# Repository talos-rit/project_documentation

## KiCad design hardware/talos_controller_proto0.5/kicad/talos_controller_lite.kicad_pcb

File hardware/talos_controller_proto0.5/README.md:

# Talos controller, prototype 0.5

A controller board for the Scorbot ER-V and ER-4pc educational arms (the Talos-RIT project's two robots), built to cost
less than the first Talos controller ([`../talos_controller/`](../talos_controller/README.md)). It drives all seven
motors of the robot (the five arm motors, the gripper and the slide rail) from an ESP32-S3-DevKitC-1 plugged into
sockets, on a 141 × 139.6 mm two-layer board that JLCPCB assembles: seven DRV8874 motor driver chips soldered on, the
encoders counted by the DevKit itself, shift registers and an analogue multiplexer in place of the expander, counter
and ADC chips, power from one 24-pin PC supply plug, and a MOTORS ON relay latch behind an external emergency stop.

The board speaks to the rest of the system through the DevKit's own USB sockets, like the first Talos controller: the
Raspberry Pi "operator" software in Eshed mode (the Eshed controller's own serial dialect), or the ROS 2 stack in
External mode (a protobuf link).

> [!warning] Status, 23 November 2026
> **Designed, checked and reviewed; never built and never powered.** The board passes KiCad's design-rule check with
> no error and nothing unconnected (six explained warnings, section 8), and separate scripted checks of the e-stop
> wiring and of the encoder lines. A separate review pass of the layout found three major and five minor points in
> the copper; all were fixed, and a re-check of the fixed board found nothing that should hold an order. JLCPCB's order page
> has seen these exact files: its parts page matched all 29 parts lines, and its placement preview showed every
> polarised part the right way round. Neither cart on [`purchase_options.md`](purchase_options.md) has been paid.
> **The firmware for this board is not published yet** (section 4). It has run on a chip only as a bench test on a
> bare DevKit: the test of the three software-counted encoders, which passed twice. Everything else (the shift
> registers, the multiplexed current reading, the drivers, the heat, the real encoders' signals) is first seen on the
> first board. Read everything here as "designed and checked, not yet proven"; section 5 exists because the first
> board is the first test of the design.

North is up. Along the west edge: the 24-pin PC supply plug `J2`, the two motor-rail capacitors `C1` and `C2`, the
MOTORS ON button `SW3`, the external e-stop terminal `J4`, the `PS_ON` jumper `JP1` and the ground post `J6`. Along the
north edge: the motor fuse `F1` ("5A MAX"), the relay `K1`, the three e-stop chain test pads (CHAIN, GND, LOOP) and the
rail terminal `J8`. In the middle, the seven drivers in a column, motor 7 at the top (`U14`) to motor 1 at the bottom
(`U8`), each with its fault lamp, its two direction lamps and its name printed beside it. East of them the shift
registers `U2`, `U3`, `U5`; then the DevKit `U1` with its USB end at the north edge, the select register `U6` under it
and the multiplexer `U7` east of it. Below the DevKit the row of ten status-LED positions, then the encoder and switch
blocks, and the 50-pin robot connector `J1` on the south edge.

## How it differs from the first Talos controller

| | First Talos controller, rev 0.5 | **This board, prototype 0.5** |
| --- | --- | --- |
| Board | 265 × 210 mm, two layers, all through-hole | **141 × 139.6 mm, two layers**, surface-mount parts placed by JLCPCB, the through-hole parts (163 joints) fitted by hand |
| Motor drivers | plug-in modules (the Talos driver module or a Pololu G2 18v17) | **one DRV8874 chip per motor, soldered on by the factory**; each limits its own current at 2.93 A (2.75 to 3.2 A over part tolerances) |
| Motor current | set by the module | **about 1.5 A in all seven motors at once without end, about 2 A in one or two** (a heat estimate, section 8) |
| Encoders | one LS7366R counter chip per motor | **the DevKit counts them itself**: four on its pulse counters (motors 1 to 4), three in software (motors 5, 6, 7) |
| Inputs, outputs, ADC | two MCP23017 expanders, two ADS1015 ADC boards | **two 74HC595 and two 74HC165 shift registers** on one SPI bus; the seven motor currents and the rail voltage through **one 74HC4051 multiplexer** into one ADC pin of the DevKit |
| Supply | 24-pin plug for 5 V, the 4-pin CPU lead for the motors, `F1` 7.5 A | **one 24-pin PC supply plug for everything**; the motors' 12 V on its pins 10 and 11; **`F1` 5 A, never more**; the firmware holds the sum of the motor currents to **4 A** |
| Emergency stop | IDEC mushroom on the board, an external loop, two relays | **external e-stop only** (screw terminal `J4`, required), **one two-pole relay**, and the drivers held asleep whenever the relay's coil is off |
| Status lights | ten through-hole pixels | per motor a red fault lamp and a pair of green direction lamps, a 5 V lamp and a motor-power lamp, all placed by JLCPCB; **ten optional 2 × 2 mm status LEDs**, fitted by hand with hot air |
| Encoder supply sense | a comparator on two DevKit pins | a divider on a shift-register input ("5 V present") |
| Firmware | the controller firmware's default board | its own board variant, not yet published (section 4) |

The robot connector `J1` is the same 50-pin socket with the same pin-out for the ER-V and the ER-4pc, and the rail
terminal `J8` is the same 8-way terminal in the same pin order.

## What is in this folder

| File | What it is |
| --- | --- |
| `README.md` | this guide |
| `parts.md` | the parts list: what JLCPCB places, what you fit by hand, the makes that fit |
| `purchase_options.md` | the two carts of 23 November 2026 (JLCPCB and Digi-Key) with every line |
| `fab/talos_controller_lite_proto0.5_gerbers.zip` and `.sha256` | the manufacturing files (Gerbers and drill files): the zip to order from. Its name is the one on the order |
| `fab/jlcpcb_bom.csv`, `fab/jlcpcb_cpl.csv` | the parts list and placement file for JLCPCB's assembly (29 lines, 241 placements) |
| `fab/hand_assembled.csv` | the parts JLCPCB does not place: what you fit yourself, with the solder joints of each |
| `fab/digikey_cart_two_boards.csv` | the Digi-Key list for two boards with spares, ready for "Upload a list" |
| `schematic.pdf` | the schematic: every part with its pins, each pin labelled with its net name |
| `images/` | `print_top.png` and `print_bottom.png` (the printed side as it will look; the bottom as seen from below), `copper_top.png` and `copper_bottom.png` (the two copper layers) |
| `kicad/` | the KiCad project: board, schematic, project file, the footprints drawn for this board and their library table. KiCad 7 format; later versions open and upgrade it |

The KiCad files keep the project's working name, `talos_controller_lite`. The schematic is generated: each part is
drawn as a pin table with net labels, not as a drawn circuit.

## What you need

- **The two orders** on [`purchase_options.md`](purchase_options.md): JLCPCB (boards, the surface-mount parts and their
  assembly) and Digi-Key (the through-hole parts). Both are for two complete boards with spares.
- **Hand soldering:** twelve through-hole positions a board (the DevKit's two socket strips counted as one), 163 joints. No surface-mount soldering is needed unless you fit
  the optional status LEDs. A multimeter; a bench supply with a current limit helps for the checks of section 5.
- **An ATX PC power supply** with a 24-pin main lead. The 4-pin CPU lead is not used.
- **An external emergency-stop button** with a normally closed contact and its cable, for `J4`. The board has no stop
  button of its own (section 6).
- **For the rail:** an adapter from the rail cable's D9 plug to bare wires for `J8`, or the plug cut off (section 6).
- **Six M3 screws and standoffs** for the six mounting holes, with plain or nylon washers on the top side (no toothed
  lock washers).
- A computer with ESP-IDF v5.5.3 to build and flash the firmware, and two micro-USB **data** cables.
- A Raspberry Pi running the operator, or a PC with the ROS 2 stack.

**Not in the carts, and needed:**

- **One ESP32-S3-DevKitC-1 per board.** Any variant that is not a "...V" part fits: N8, N8R2, N8R8, N16R8 and their
  1U versions (an antenna socket in place of the printed antenna; the board does not use the radio). The R8 variants
  use GPIO35 to GPIO37 for their memory, and the board leaves those three pins unconnected. **A variant ending in V
  (N16R8V, N32R16V) must not be used**: it runs GPIO47 and GPIO48 at 1.8 V, and this board uses both (encoder 4 and
  the status-LED data).
- **Optional: ten status LEDs, 2.0 × 2.0 mm, WS2812-type** (positions `D21` to `D28`, `D49`, `D50`), fitted by hand
  with hot air; JLCPCB's Economic assembly does not place this kind of part, so the factory leaves the positions empty
  and the board works without them. The footprint and the firmware's timing were drawn for the Worldsemi
  WS2812C-2020-V6 (5 mA per colour); the Worldsemi **WS2812B-2020** fits the same pads with the same pin map and
  timing, at **12 mA per colour**. What they need:
  - **Pin 1 on the pad with the printed dot** beside it. Pins: 1 data out, 2 ground, 3 data in, 4 supply (5 V).
  - **They are moisture sensitive** (class 5a in Worldsemi's sheet): bake loose parts before hot air (Worldsemi
    gives 120 °C for 4 h) or take the risk on a cheap part.
  - **Fit one first** and check that it lights and passes data on before fitting the others.
  - **Keep the firmware's brightness cap** (32 of 255). At the cap ten WS2812B-2020 take about 50 mA; at full white
    they would take about 0.37 A, which the 5 V fuse `F3` carries but with little margin in a warm box.

## 1. Order the board

Upload `fab/talos_controller_lite_proto0.5_gerbers.zip` to JLCPCB as it is; check its sha256 against
`fab/talos_controller_lite_proto0.5_gerbers.zip.sha256` first if you copied it around. The cart of
[`purchase_options.md`](purchase_options.md) was made with these options:

| Option | Choose |
| --- | --- |
| Layers, size | 2 layers; 141 × 139.6 mm is read from the files. The bottom edge has a notch 69 × 2.8 mm under the robot connector, on purpose (section 3) |
| Thickness, colour | 1.6 mm, green |
| Copper | 1 oz outer copper (every current and heat figure here assumes 1 oz) |
| Surface finish | the cart was priced with JLCPCB's default, leaded HASL; lead-free HASL is a choice on the order page, not priced here |
| Design limits | tracks and gaps 0.2 mm or more, vias 0.6 / 0.3 mm, smallest hole 0.3 mm: inside JLCPCB's standard two-layer service |
| Order number | **"Specify a location"**: the board has a text `JLCJLCJLCJLC` under its name for it; otherwise JLCPCB prints the number where it likes |
| Quantity | 5 bare boards, 2 of them assembled (the cart's choice) |

Expect one remark: 34 part references on the top side are printed 0.8 mm high, under JLCPCB's recommended 1.0 mm.
All of them are references of parts the factory places; every function text is 1.0 mm or more.

**Assembly.** PCB assembly, **Economic, top side**. Upload `fab/jlcpcb_bom.csv` as the BOM and `fab/jlcpcb_cpl.csv`
as the placement file. The parts page should read "29 parts detected, 29 parts confirmed"; eight of the lines are
Extended parts (with JLCPCB's fee per part type): `D1`, the BAT54S, `F2`, `F3`, the 47 Ω 1 W resistor, the 74HC165,
the 74HC4051 and the DRV8874. JLCPCB adds its own spares or minimum quantities on some lines. A line it cannot match
or has no stock for must be resolved before ordering: every placed part is surface-mount, and the drivers need hot
air.

Choose **Confirm parts placement = Yes** and check the preview: the seven drivers (pin 1 at the south-east, the chips
are turned half round), the five SOIC-16 chips `U2`, `U3`, `U5`, `U6`, `U7` (pin 1 at the north-west), the fourteen
BAT54S, `Q3` and `Q4`, the 23 lamps (the preview's "+" at the anode, the end opposite pad 1) and the diodes `D1`, `D4`,
`D20` (the band at pad 1). The ten status-LED positions stay empty.

## 2. Order the parts

[`purchase_options.md`](purchase_options.md) has both carts line by line. For Digi-Key, upload
`fab/digikey_cart_two_boards.csv` with "Upload a list"; it is the list the cart was made from (14 lines, two boards,
with spare fuses, relay, switch and capacitors). [`parts.md`](parts.md) has every part, the makes that fit and the
rules that must not be broken when substituting. The three most important:

- **`F1` is a 5 A blade fuse, never more** (section 6 says why).
- **The supply header `J2`**: try the PC supply's plug in a loose header before soldering it (Würth's make).
- **The robot connector `J1`**: seat it in a bare board before soldering (HARTING's make).

## 3. Assemble

JLCPCB places every surface-mount part. You fit the through-hole parts of `fab/hand_assembled.csv`, all from the top,
soldered on the bottom, where every through-hole pin has its name printed. Lowest parts first:

1. **`JP1` and `J6`**: two 2-pin pieces cut from the 1×40 header strip. A shunt on `JP1` ("PS_ON, FIT = ON") turns
   the supply on with its own mains switch.
2. **The DevKit's two 1×22 socket strips** (`U1`). Solder two end pins of each, check that the DevKit seats with its
   USB end at the printed "DEVKIT USB END" and triangle, then the rest.
3. **`SW3`, MOTORS ON** (Omron B3F-4055; its two bosses go into the two holes), then its key top.
4. **`C1` and `C2`, 220 µF 35 V. Mind the polarity**: the long lead (+) goes in the square pad, marked "+" on both
   sides; the filled half of the printed outline is the ground side.
5. **`J4`, the e-stop terminal** (2 pins, 5.08 mm). If the Same Sky part does not go into the holes, two wires can be
   soldered in its place.
6. **`J8`, the rail terminal**, wire entry towards the north edge. Hold the part against the board before soldering.
   Its motor pins (`M+`, `M−`) carry the rail motor's 12 V: look at every joint for a bridge.
7. **`F1`, the fuse holder**, and **`K1`, the relay**.
8. **`J2`, the 24-pin supply header.** **First push the PC supply's plug into the loose header** and check it latches
   (Würth's data sheet gives the board's hole pattern but does not say the part mates with the supply's plug; Molex's
   39-30-1240 is a verified second make, see `parts.md`). Its pegs are plastic: a substitute with a metal board-lock
   must not be used, because 12 V and e-stop copper pass close to the peg holes. The housing is flush with the west
   edge.
9. **`J1`, the robot connector, last.** **Seat it in the bare board before soldering**: HARTING's 09 66 552 6616, on
   the Digi-Key list, has a threaded flange that reaches below the board's top face, which is why the bottom edge
   steps back 2.8 mm under the connector; its fit was checked against HARTING's 3D model, not a real part. Amphenol's
   DD50S565MTLF fits as well (with two screwlock kits). The pads are close together (0.23 mm to the nearest other
   copper at one place): solder with a fine tip and inspect every joint under a magnifier.
10. **The fuse**: a 5 A ATO blade into `F1`. The 0.5 A chain fuse `F2` and the 1.5 A resettable fuse `F3` are
    soldered by the factory.
11. **The DevKit**, with its USB end at the printed "DEVKIT USB END" and triangle (the north edge). **Turned round it
    still fits, and its 5 V and ground pins land on other nets.**
12. **Mounting:** six M3 screws with plain or nylon washers on the top side, no toothed lock washers. No copper on
    the outer layers comes within 3.6 mm of a hole's centre, so metal washers are fine.

Trim the e-stop wires clean when you clamp them in `J4`: its two pins are 2.5 mm apart, and a wire strand across them
bypasses the external stop without a sign.

## 4. Firmware

> [!warning] Not published yet
> This board needs its own variant of the Scorbot Controller firmware, the firmware of the first Talos controller
> ([talos-rit/esp-driver](https://github.com/talos-rit/esp-driver)): seven motors, the pin plan below, the
> shift-register words, three software-counted encoders and the multiplexed current reading. That variant is written
> but not published: **not yet implemented in the published firmware (prototype 0.5 board variant, to be
> published)**. It passes the firmware's host tests and compiles for the ESP32-S3 with ESP-IDF v5.5.3 with no warnings;
> on a chip it has run only as the encoder bench test below. Do not flash the first Talos controller's firmware onto this board: its pins are
> not this board's.

**The encoder bench test.** On a bare DevKit with nothing on its pins, the chip makes a quadrature signal on the three
software-counted encoders' pin pairs and a hardware pulse counter counts the same signal as the reference, while the
firmware is kept busier than in service. It passed twice, with the software count equal to the hardware count and no
illegal step at every rate from 8,000 to 128,000 counts a second (31.7 million edges on each encoder); 8,000 counts a
second is the assumed top speed of one encoder (80 counts per motor turn at an assumed 6,000 motor turns a minute,
not measured). The encoders are handled by an interrupt at level 5; the firmware must keep it (lower levels lost
counts on the bench). The test does not show three encoders moving independently (its three pairs carried one
signal), the real encoders' signals, or a line that chatters.

**The link.** The DevKit's socket marked **UART** is the link to the Pi and the flashing port; the socket marked
**USB** is the console. In Eshed mode the board speaks the Eshed controller's serial dialect at 9600 baud, so the
operator on the Pi runs unchanged; External mode is the protobuf link used by the ROS 2 stack. The ESP32-S3's ROM
prints a boot log on the UART socket at every reset; the first Talos controller's guide (section 4) has the eFuse
setting that silences it.

**eFuses never to burn on a DevKit used here:** `STRAP_JTAG_SEL` (GPIO3 is an encoder input on this board; with that
fuse, its level at reset would move JTAG onto GPIO39 to GPIO42, which are `PWM5`, encoder 2 and `SLP`) and
`DIS_USB_JTAG` (the console).

### Pin plan

The contract between the board and the firmware. No GPIO is left free.

| GPIO | Net | Use |
| --- | --- | --- |
| 1, 2 / 41, 40 / 4, 5 / 47, 21 | `ENC1A`/`B` to `ENC4A`/`B` | encoders 1 to 4, on the pulse counters |
| 11, 12 / 6, 7 / 8, 3 | `ENC5A`/`B`, `ENC6A`/`B`, `ENC7A`/`B` | encoders 5 to 7, counted in software (GPIO3 is a strapping pin; its 10 kΩ pull-up holds it high at reset) |
| 15, 16, 17, 18, 39 | `PWM1` to `PWM5` | drivers 1 to 5, `EN` input (PWM) |
| 38 | `PWM6` | driver 6 (gripper); on DevKit v1.1 also the DevKit's own RGB LED, which then flickers while the gripper moves |
| 9 | `PWM7` | driver 7 (rail) |
| 10 | `AMUX` | ADC1 channel 9: the multiplexer's output |
| 42 | `SLP` | the drivers' sleep line, through the transistor `Q3` (section 6) |
| 14, 46, 13, 45 | `SR_SCK`, `SR_MOSI`, `SR_MISO`, `SR_LATCH` | the four shift registers, SPI mode 0, 1 MHz or less (45 and 46 are strapping pins; they only drive logic inputs) |
| 48 | `PIX_3V` | status-LED data, through the level shifter `Q4` to 5 V; on DevKit v1.0 also the DevKit's own RGB LED |
| 0, 19, 20, 35 to 37, 43, 44 | not connected | the BOOT button, the USB socket, the R8 modules' memory, UART0 (the Pi link) |

**Output word** (16 bits, MSB first): bits 10, 9, 8 the multiplexer's channel (`U6`), bits 7 to 1 `DIR7` to `DIR1`
(`U2`), all other bits 0. **Input word** (16 bits, bit 15 first in): 15 to 12 `NFLT4` to `NFLT1`, 11 tied low (the
word's one check bit), 10 and 9 `NFLT7` and `NFLT6`, 8 `NFLT5` (each 0 = driver fault); 7 to 4 `SW4` to `SW1`, 3 `SW7`
(the rail), 2 "5 V present", 1 e-stop loop closed, 0 `SW5`. The gripper has no switch.

**The multiplexer `U7`** (74HC4051, on 3.3 V): channels 0 to 6 are the motor currents 1 to 7 at 0.45 V per ampere
(1.32 V at the drivers' 2.93 A limit), channel 7 the motor rail divided by 11 (1.09 V at 12 V). Each input has its own
10 kΩ / 100 nF filter in front of the multiplexer; the planned timing converts one input per 1 ms control period, so
each line is read every 8 ms, at least 10 µs after the select lines change.

## 5. First power, in order

Nothing is connected to a robot before these pass. Test pads, bare copper with their names printed: CHAIN, GND and
LOOP north of the relay, COIL beside the coil's diode, 12V, 5V, VM (the motor rail), 3V3, SLEEP, and a second GND;
`J6` is a ground post for a scope clip.

1. **Look first.** Under a magnifier: the robot connector's pins (motor pins pass close to other copper), the rail
   terminal's motor pins, the e-stop terminal's two pins, the DevKit socket strips.
2. **Continuity, unpowered, nothing plugged in, `J4` empty:**
   - CHAIN to LOOP: **no continuity.** A beep is a bridge across `J4` and bypasses the external stop.
   - LOOP to COIL: **no continuity.** A beep means MOTORS ON or the relay's latch contact is bridged.
   - Each motor lead at `J1` (and `M+`, `M−` at `J8`) against ground: no short.
3. **Supply on, no DevKit, no robot cable, `J4` empty.** The 5 V lamp lights; 5V reads about 5 V, 12V and CHAIN
   about 12 V, LOOP and VM 0 V, the motor-power lamp is dark. Press MOTORS ON: **nothing happens** (the chain is
   open at `J4`). If the relay pulls in, switch off and find the bridge.
4. **The e-stop test, on every board that is built.** Fit the external e-stop (or, for this bench test only, a wire
   link) in `J4`. LOOP now reads about 12 V; the relay must stay off until MOTORS ON is pressed. Press it:
   the relay latches, VM reads about 12 V and the motor-power lamp lights. Open the e-stop (or take a link out): the relay drops and VM
   falls below 9 V within about a quarter of a second. Close it again: **the relay must stay off until MOTORS ON is pressed again.**
   Any other result is a fail; do not connect motors to that board.
5. **Supply off, DevKit in** (USB end at the north edge, as printed), supply on: 3V3 reads 3.3 V. The fault lamps
   may glow while the motor rail is off; what they do then is not known yet.
6. **Firmware**, with no robot: flash, read the console. With the board's 5 V present the encoders' "5 V present"
   input reads high; with only a USB cable in and the PC supply off, the DevKit runs but the encoders are dark (the
   board's 5 V reaches the DevKit through a Schottky diode, so USB cannot feed the board).
7. **One motor, with its encoder**, before the arm: direction for a positive command, the encoder's count against a
   turn by hand, the current reading against a meter. Compare a software-counted encoder (motors 5, 6, 7) with a
   hardware-counted one on the same signal if you can. Measure the drivers' temperature at 1, 1.5 and 2 A.
8. **Then the arm.**

## 6. Connect the robot

- **Power: the PC supply's 24-pin lead into `J2`.** It is the only supply input. The motors' 12 V comes through its
  pins 10 and 11, 5 V through pins 21 to 23, and `PS_ON` (pin 16) goes to the jumper `JP1`. The supply's unused pins
  are live on the supply's side.

> [!danger] `F1` is never more than 5 A
> One pin of the 24-pin connector is rated 6 A, and Molex states that its pins are not designed to share current, so
> one of the two 12 V pins must be able to carry all of it. The label at the fuse reads "5A MAX". With a larger fuse a
> fault can overheat a connector pin before the fuse opens. The firmware holds the sum of the motor currents to 4 A, so
> in normal use the fuse is never the first thing to act.

- **The external emergency stop, `J4`** ("E-STOP, NC SWITCH OR LINK"). A normally closed button: one wire per clamp.
  **The board has no stop button of its own; a wire link in `J4` defeats the stop** and is for the bench test of
  section 5 only. Without either, MOTORS ON does nothing, which is intended.
- **MOTORS ON (`SW3`).** After power-up the motor rail is off. MOTORS ON pulls the relay in and its second pole holds
  it. Opening the e-stop or losing power drops it, and it stays off until MOTORS ON is pressed again. The relay's coil
  also feeds the gate of `Q3`: while the coil is off, every driver is held asleep (outputs off) whatever the firmware
  does. The e-stop chain has its own 0.5 A fuse, `F2`, soldered on the board: a short from the e-stop wiring to ground
  blows it, and the motors then stay off until it is replaced (spares are on the Digi-Key list; replace it with an
  iron).
- **`J1`, the 50-pin robot connector:** the robot's own cable plugs in directly; the pin-out is the first Talos
  controller's, the same for the ER-V and the ER-4pc. Motors 1 to 5 are the arm, motor 6 the gripper: motor on pins
  45 (+) and 12 (−), encoder on 34 and 19, its LED supply on 25, ground on 28; the gripper has no switch.
- **`J8`, the rail (motor 7):** the slide rail's cable ends in a D9 plug, and `J8` takes bare wires, so it needs an
  adapter (a D9 socket with wires) or its plug cut off. None exists yet.

  | `J8` screw | 1 | 2 | 3 | 4 | 5 | 6 | 7 | 8 |
  | --- | --- | --- | --- | --- | --- | --- | --- | --- |
  | Printed | M+ | M− | LED | A | B | SW | GND | GND |
  | Signal | motor + | motor − | encoder LED supply | encoder A | encoder B | switch | ground | ground |
  | Rail's D9 pin | 1 | 9 | 3 | 8 | 6 | 4 | 5 | shield |

  A wrong wire on the board side damages nothing: a motor lead on an encoder or switch screw is 12 V behind 1 kΩ and a
  clamp diode, the LED screw on ground is 0.53 W in a 1 W resistor, a motor lead on ground trips the driver.
- **The Pi:** a USB data cable from the Pi to the DevKit's UART socket. Leave the USB (console) socket unplugged in
  normal use, or connect a PC to read the logs.

## 7. Indicators

These need no firmware:

- **5 V lamp** (green, "5V" by `D3`): the board's 5 V is up.
- **Motor-power lamp** (green, "MOTORS" by `D2`): the motor rail is live (MOTORS ON latched).
- **Fault lamp per motor** (red, "FLT"): lit while that driver reports a fault (over-current, over-temperature). A chip that overheats turns its outputs off, lights this lamp and turns them on again when it has cooled.
- **Direction lamps per motor** (green, "+" and "−"): which way that driver's outputs drive, with a brightness that
  follows the PWM; both dark while the driver brakes or sleeps. A motor turned by hand with the board off lights them
  from its own voltage.

The ten optional status LEDs, printed `MOTOR 1` to `MOTOR 7`, `SYS`, `LINK`, `E-STOP` below the DevKit, follow the
status scheme of the first Talos controller's guide (section 7); the firmware drives them.

## 8. Open items and known limitations

- **Nothing has been built.** The first board is the first test of every footprint, of the e-stop chain, the shift
  registers' timing, the multiplexed current reading and the heat figures. Expect to find something.
- **The firmware for this board is not published** (section 4), and has run on a chip only as the encoder bench test.
- **Three encoders are counted in software** (5 wrist, 6 gripper, 7 rail). Not shown yet: three encoders moving
  independently, the real encoders' signals, and a line that chatters; the software-counted lines have no glitch
  filter beyond their 1 kΩ and 1 nF, and a chattering line can hold one of the chip's two cores at interrupt level 5.
  The firmware's count of illegal steps does not see every lost count (a handler three or four edges late loses four
  counts without one); an in-service check against lost counts is not yet implemented (firmware work list).
- **The encoders' low level.** The input circuit gives about 0.3 V plus nine tenths of the encoder's own low level;
  a low of about 0.6 V at the pin is expected against the 0.83 V the chip guarantees to read as low. To be measured
  on the first board.
- **Motor current, an estimate.** By a heat model of this board (not a measurement, about ±15 % on the currents, 1 oz
  copper): all seven motors at once without end about 1.5 A each (the model's limit is about 1.8 A, 1.7 A in a 40 °C
  box); one or two motors at 2 A fine. The firmware's 4 A sum cap keeps all seven far below that (about 40 °C at the
  chips). **One motor held stalled at its 2.93 A chop current, which the cap allows, can take its chip into thermal
  shutdown** (the fault lamp lights, the motor stutters); stopping a stalled joint is the firmware's job.
- **The 4 A cap is shared by all seven motors.** The rail peaks at about 2.2 A in normal use, which leaves about 1.8 A
  for the arm; the cap then slows every joint together. Move the rail with the arm still.
- **Current readings every 8 ms per motor** (one ADC pin for eight inputs): the firmware's over-current fault comes
  after about 50 ms; each driver chip limits its own current in hardware meanwhile.
- **One check bit in the input word** (bit 11): a word shifted by one bit goes unnoticed while driver 1 or driver 7
  reports a fault.
- **The gripper has no switch.** Homing it against its closing stop is not yet implemented in the published firmware
  (firmware work list); the gripper's and the rail's numbers (ratios, limits) have not been measured, and until they
  are, those two motors are not moved.
- **The rail's switch**: whether it is normally closed, or its leads simply joined, is not known; the firmware's switch
  polarity is one setting for all motors.
- **The wrist.** Motors 4 and 5 drive the wrist as a pair (opposite ways tilt it, the same way twists it), so the
  board's print names both "WRIST". The conversion between the two motors and the wrist's two joints is not yet
  implemented in the firmware (firmware work list).
- **A welded relay.** `K1` is one two-pole relay, not a force-guided type. If its power contact welds, the stop still
  works (the coil drops and the drivers are held asleep), but the latch contact can stay closed too, and closing the
  e-stop again would then pull the relay in without MOTORS ON. A firmware rule that latches a fault in that state (e-stop
  open, motor rail still up after a few seconds) is not yet implemented (firmware work list).
- **Relay inrush.** The relay closes onto 2 × 220 µF and the drivers' 10 µF capacitors at every MOTORS ON. Whether
  its contacts take that over its life is not known.
- **The e-stop chain's guard tracks are under solder mask.** Ground tracks run between the chain's three wires, so a
  copper fault between them blows `F2` instead of bypassing the stop. They do not stop a solder blob or a wire strand
  across bare pads: the e-stop test of section 5 on every board is what covers that.
- **The 5 V budget**: worst case about 0.5 A at the firmware's LED cap, about 0.83 A with ten WS2812B-2020 at full
  white, against `F3`'s 1.5 A hold (less when warm). Measure the 5 V current at first power.
- **Parts checked on paper only:** HARTING's robot connector against its 3D model; Würth's supply header against its
  data sheet's hole pattern (not its mating with the plug); the Same Sky e-stop terminal against nothing (its drawing
  was not available). Section 3 says what to try before soldering.
- **The DevKit's own RGB LED** shares a pin with the board on both DevKit versions: on v1.1 (`RGB@IO38` printed by the
  LED) it flickers while the gripper moves; on v1.0 (`RGB@IO48`) it shows the first status LED's data. Cosmetic.
- **The design-rule check's six warnings**: five ground pins of the robot connector's middle row (29 to 33) join the
  top ground fill with one spoke instead of two (they are also in the bottom ground), and the status LEDs' 5 V track
  runs 1.5 mm past the last LED.
- **Print:** 34 part references on the top side are 0.8 mm high, under JLCPCB's recommended 1.0 mm.
- **The schematic** is a generated pin table per part, not a drawn circuit.

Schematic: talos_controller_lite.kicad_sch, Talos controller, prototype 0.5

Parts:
C1, C2: 220uF 35V; CP_Radial_D8.0mm_P3.50mm; MPN any of that size (for example Nichicon 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
C3, C4, C32, C33, C52, C53, C54, C55, C56, C60, C65: 10uF 25V; C_0805_2012Metric; MPN generic 0805 10uF 25V; LCSC C15850
C5, C6, C8, C9, C10, C11, C12, C13, C14, C15, C16, C18, C19, C21, C22, C24, C25, C27, C28, C30, C31, C34, C35, C36, C47, C48, C49, C50, C51, C58, C59, C61, C63, C64, C66, C71, C72, C73: 100nF; C_0603_1608Metric; MPN generic 0603 100nF; LCSC C14663
C7: 10nF; C_0603_1608Metric; MPN generic 0603 10nF; LCSC C57112
C17, C20, C23, C26, C29, C57, C62: 22nF; C_0603_1608Metric; MPN generic 0603 22nF; LCSC C21122
C37, C38, C39, C40, C41, C42, C43, C44, C45, C46, C67, C68, C69, C70: 1nF; C_0603_1608Metric; MPN generic 0603 1nF; LCSC C1588
D1: SMBJ15A; D_SMB; MPN SMBJ15A; LCSC C2760888
D2, D3, D5, D6, D8, D9, D11, D12, D14, D15, D17, D18, D39, D40, D42, D43: green; LED_0805_2012Metric; MPN Hubei KENTO KT-0805G; LCSC C2297
D4: 1N4148W; D_SOD-123; MPN 1N4148W; LCSC C81598
D7, D10, D13, D16, D19, D41, D44: red; LED_0603_1608Metric; MPN Hubei KENTO KT-0603R; LCSC C2286
D20: B5819W; D_SOD-123; MPN B5819W; LCSC C8598
D21, D22, D23, D24, D25, D26, D27, D28, D49, D50: WS2812C; LED_WS2812B-2020_PLCC4_2.0x2.0mm; MPN Worldsemi WS2812C-2020-V6; LCSC C55109522
D29, D30, D31, D32, D33, D34, D35, D36, D37, D38, D45, D46, D47, D48: BAT54S; SOT-23; MPN Nexperia BAT54S,215; LCSC C47546
F1: ATO 5 A; FuseHolder_Blade_ATO_Littelfuse_FLR_178.6165; MPN Littelfuse 178.6165.0001
F2: 0.5 A fast; Fuse_1206_3216Metric; MPN Littelfuse 0466.500NRHF; LCSC C151133
F3: PTC 1.5 A; Fuse_1812_4532Metric; MPN Littelfuse MINISMDC150F-2; LCSC C9308
J1: ROBOT D50; Amphenol_D50S82C6GX00LF; MPN Amphenol DD50S565MTLF (or HARTING 09 66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
J2: ATX 24-pin; Molex_Mini-Fit_Jr_5569-24A2_2x12_P4.20mm_Horizontal; MPN Wuerth 649024227222 (or Molex 003930024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
J4: E-STOP (NC); TerminalBlock_Phoenix_MKDS-1,5-2-5.08_1x02_P5.08mm_Horizont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; MPN Phoenix Contact MKDS 1,5/2-5,08 (171572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
J6: GND post; PinHeader_1x02_P2.54mm_Vertical; MPN Sullins PRPC040SAAN-RC, two pins of it
J8: RAIL; TerminalBlock_Phoenix_MKDS-1,5-8-5.08_1x08_P5.08mm_Horizont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; MPN Phoenix Contact MKDS 1,5/ 8-5,08 (17157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
JP1: PS_ON (fit = on); PinHeader_1x02_P2.54mm_Vertical; MPN Sullins PRPC040SAAN-RC, two pins of it
K1: G2RL-2 12V; Relay_DPDT_Omron_G2RL-2; MPN Omron G2RL-2 DC12
Q3, Q4: 2N7002; SOT-23; MPN 2N7002; LCSC C8545
R1, R2, R19: 3k; R_0603_1608Metric; MPN generic 0603 3k; LCSC C4211
R3, R20, R27, R28, R32, R33, R37, R38, R42, R43, R47, R48, R89, R90, R96, R97: 4.7k; R_0603_1608Metric; MPN generic 0603 4.7k; LCSC C23162
R4: 2.2k; R_0603_1608Metric; MPN generic 0603 2.2k; LCSC C4190
R5, R11, R13: 100k; R_0603_1608Metric; MPN generic 0603 100k; LCSC C25803
R6: 30k; R_0603_1608Metric; MPN generic 0603 30k; LCSC C22984
R7, R9, R14, R15, R16, R17, R18, R21, R22, R23, R24, R25, R26, R55, R57, R59, R61, R63, R65, R67, R69, R71, R73, R75, R77, R79, R81, R83, R94, R95, R101, R102, R104, R106, R108, R110, R112: 10k; R_0603_1608Metric; MPN generic 0603 10k; LCSC C25804
R8, R12, R30, R35, R40, R45, R50, R52, R53, R54, R56, R58, R60, R62, R64, R66, R68, R70, R72, R74, R76, R78, R80, R82, R92, R99, R103, R105, R107, R109, R111: 1k; R_0603_1608Metric; MPN generic 0603 1k; LCSC C21190
R10: 47k; R_0603_1608Metric; MPN generic 0603 47k; LCSC C25819
R29, R34, R39, R44, R49, R91, R98: 1.5k; R_0603_1608Metric; MPN generic 0603 1.5k; LCSC C22843
R31, R36, R41, R46, R51, R93, R100: 470; R_0603_1608Metric; MPN generic 0603 470; LCSC C23179
R84, R85, R86, R87, R88, R113, R114: 47 1W; R_2512_6332Metric; MPN 25121WJ0470T4E; LCSC C15261
SW3: MOTORS ON; SW_PUSH-12mm_B3F; MPN Omron B3F-4055 + B32-1310
TP1: CHAIN; TestPoint_Pad_D1.5mm
TP2, TP10: GND; TestPoint_Pad_D1.5mm
TP3: LOOP; TestPoint_Pad_D1.5mm
TP4: COIL; TestPoint_Pad_D1.5mm
TP5: VM; TestPoint_Pad_D1.5mm
TP6: 12V; TestPoint_Pad_D1.5mm
TP7: 5V; TestPoint_Pad_D1.0mm
TP8: 3V3; TestPoint_Pad_D1.0mm
TP9: SLEEP; TestPoint_Pad_D1.5mm
U1: ESP32-S3-DevKitC-1; ESP32_S3_DevKitC_1_sockets; MPN Espressif ESP32-S3-DevKitC-1
U2, U6: 74HC595; SOIC-16_3.9x9.9mm_P1.27mm; MPN Nexperia 74HC595D,118; LCSC C5947
U3, U5: 74HC165; SOIC-16_3.9x9.9mm_P1.27mm; MPN Nexperia 74HC165D,653 (no substitute); LCSC C5613
U7: 74HC4051; SOIC-16_3.9x9.9mm_P1.27mm; MPN Texas Instruments CD74HC4051M96; LCSC C132065
U8, U9, U10, U11, U12, U13, U14: DRV8874; HTSSOP-16-1EP_DRV8874_PWP; MPN Texas Instruments DRV8874PWPR; LCSC C1855818

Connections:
5V_ATX: F3.1, J2.21 (+5V), J2.22 (+5V), J2.23 (+5V)
5V_OK: R19.2, R20.1, U5.13 (C)
5V_U1: D20.1 (K), U1.21 (5V)
12V_ATX: F1.1 (IN), J2.10 (+12V), J2.11 (+12V)
12V_CHAIN: F2.2, J4.1, TP1.1
+3V3: C8.2, C9.2, C10.2, C33.2, C72.2, C73.2, D29.2 (K), D30.2 (K), D31.2 (K), D32.2 (K), D33.2 (K), D34.2 (K), D35.2 (K), D36.2 (K), D37.2 (K), D38.2 (K), D45.2 (K), D46.2 (K), D47.2 (K), D48.2 (K), Q4.1 (G), R14.1, R15.1, R16.1, R17.1, R18.1, R31.1, R36.1, R41.1, R46.1, R51.1, R55.2, R57.2, R59.2, R61.2, R63.2, R65.2, R67.2, R69.2, R71.2, R73.2, R75.2, R77.2, R79.2, R81.2, R83.2, R93.1, R94.1, R100.1, R101.1, R104.2, R106.2, R108.2, R110.2, R112.2, TP8.1, U1.1 (3V3), U1.2 (3V3), U2.10 (SRCLR/), U2.16 (VCC), U3.16 (VCC), U5.16 (VCC), U6.10 (SRCLR/), U6.16 (VCC), U7.16 (VCC), U8.5 (VREF), U9.5 (VREF), U10.5 (VREF), U11.5 (VREF), U12.5 (VREF), U13.5 (VREF), U14.5 (VREF)
+5V: C32.1, C34.2, C35.2, C36.2, D20.2 (A), D21.4 (VDD), D22.4 (VDD), D23.4 (VDD), D24.4 (VDD), D25.4 (VDD), D26.4 (VDD), D27.4 (VDD), D28.4 (VDD), D49.4 (VDD), D50.4 (VDD), F3.2, R4.1, R19.1, R53.2, R84.1, R85.1, R86.1, R87.1, R88.1, R113.1, R114.1, TP7.1
+12V_F: F1.2 (OUT), F2.1, K1.21 (COM2), TP6.1
AMUX: U1.16 (IO10), U7.3 (Z)
COIL: D4.1 (K), K1.14 (NO1), K1.A1 (COIL), R10.2, SW3.2, TP4.1
CPH1: C17.2, U8.13 (CPH)
CPH2: C20.2, U9.13 (CPH)
CPH3: C23.2, U10.13 (CPH)
CPH4: C26.2, U11.13 (CPH)
CPH5: C29.2, U12.13 (CPH)
CPH6: C57.2, U13.13 (CPH)
CPH7: C62.2, U14.13 (CPH)
CPL1: C17.1, U8.14 (CPL)
CPL2: C20.1, U9.14 (CPL)
CPL3: C23.1, U10.14 (CPL)
CPL4: C26.1, U11.14 (CPL)
CPL5: C29.1, U12.14 (CPL)
CPL6: C57.1, U13.14 (CPL)
CPL7: C62.1, U14.14 (CPL)
CS1: R21.1, R29.1, R30.2
CS2: R22.1, R34.1, R35.2
CS3: R23.1, R39.1, R40.2
CS4: R24.1, R44.1, R45.2
CS5: R25.1, R49.1, R50.2
CS6: R91.1, R92.2, R95.1
CS7: R98.1, R99.2, R102.1
DIR1: U2.1 (QB), U8.2 (PH/IN2)
DIR2: U2.2 (QC), U9.2 (PH/IN2)
DIR3: U2.3 (QD), U10.2 (PH/IN2)
DIR4: U2.4 (QE), U11.2 (PH/IN2)
DIR5: U2.5 (QF), U12.2 (PH/IN2)
DIR6: U2.6 (QG), U13.2 (PH/IN2)
DIR7: U2.7 (QH), U14.2 (PH/IN2)
ENC1A: C40.1, D32.3 (COM), R60.2, R61.1, U1.26 (IO1)
ENC1A_IN: J1.2, R60.1
ENC1B: C37.1, D29.3 (COM), R54.2, R55.1, U1.27 (IO2)
ENC1B_IN: J1.5, R54.1
ENC2A: C41.1, D33.3 (COM), R62.2, R63.1, U1.29 (IO41)
ENC2A_IN: J1.1, R62.1
ENC2B: C42.1, D34.3 (COM), R64.2, R65.1, U1.30 (IO40)
ENC2B_IN: J1.21, R64.1
ENC3A: C44.1, D36.3 (COM), R68.2, R69.1, U1.4 (IO4)
ENC3A_IN: J1.36, R68.1
ENC3B: C38.1, D30.3 (COM), R56.2, R57.1, U1.5 (IO5)
ENC3B_IN: J1.4, R56.1
ENC4A: C45.1, D37.3 (COM), R70.2, R71.1, U1.39 (IO47)
ENC4A_IN: J1.35, R70.1
ENC4B: C43.1, D35.3 (COM), R66.2, R67.1, U1.40 (IO21)
ENC4B_IN: J1.20, R66.1
ENC5A: C46.1, D38.3 (COM), R72.2, R73.1, U1.17 (IO11)
ENC5A_IN: J1.18, R72.1
ENC5B: C39.1, D31.3 (COM), R58.2, R59.1, U1.18 (IO12)
ENC5B_IN: J1.3, R58.1
ENC6A: C67.1, D45.3 (COM), R103.2, R104.1, U1.6 (IO6)
ENC6A_IN: J1.34, R103.1
ENC6B: C68.1, D46.3 (COM), R105.2, R106.1, U1.7 (IO7)
ENC6B_IN: J1.19, R105.1
ENC7A: C69.1, D47.3 (COM), R107.2, R108.1, U1.12 (IO8)
ENC7A_IN: J8.4 (A), R107.1
ENC7B: C70.1, D48.3 (COM), R109.2, R110.1, U1.13 (IO3)
ENC7B_IN: J8.5 (B), R109.1
ESTOP_LOOP: J4.2, K1.11 (COM1), R6.1, SW3.1, TP3.1
ESTOP_SENSE: C6.1, R6.2, R7.1, U5.12 (B)
GND: C1.2 (-), C2.2 (-), C3.2, C4.2, C5.1, C6.2, C7.2, C8.1, C9.1, C10.1, C11.1, C12.1, C13.1, C14.1, C15.1, C16.1, C19.2, C22.2, C25.2, C28.2, C31.2, C32.2, C33.1, C34.1, C35.1, C36.1, C37.2, C38.2, C39.2, C40.2, C41.2, C42.2, C43.2, C44.2, C45.2, C46.2, C47.2, C48.2, C49.2, C50.2, C51.2, C52.1, C53.1, C54.1, C55.1, C56.1, C59.2, C60.1, C61.1, C64.2, C65.1, C66.1, C67.2, C68.2, C69.2, C70.2, C71.2, C72.1, C73.1, D1.2 (A), D2.1 (K), D3.1 (K), D4.2 (A), D21.2 (GND), D22.2 (GND), D23.2 (GND), D24.2 (GND), D25.2 (GND), D26.2 (GND), D27.2 (GND), D28.2 (GND), D29.1 (A), D30.1 (A), D31.1 (A), D32.1 (A), D33.1 (A), D34.1 (A), D35.1 (A), D36.1 (A), D37.1 (A), D38.1 (A), D45.1 (A), D46.1 (A), D47.1 (A), D48.1 (A), D49.2 (GND), D50.2 (GND), J1.28, J1.29, J1.30, J1.31, J1.32, J1.33, J1.SH1, J1.SH2, J2.3 (COM), J2.5 (COM), J2.7 (COM), J2.15 (COM), J2.17 (COM), J2.18 (COM), J2.19 (COM), J2.24 (COM), J6.1, J6.2, J8.7 (GND), J8.8 (GND), JP1.2, K1.A2 (COIL), R1.2, R2.2, R7.2, R9.2, R11.2, R13.1, R20.2, R26.2, R30.1, R35.1, R40.1, R45.1, R50.1, R92.1, R99.1, TP2.1, TP10.1, U1.22 (GND), U1.23 (GND), U1.43 (GND), U1.44 (GND), U2.8 (GND), U2.13 (OE/), U3.8 (GND), U3.14 (D), U3.15 (CLK INH), U5.8 (GND), U5.10 (SER), U5.15 (CLK INH), U6.8 (GND), U6.13 (OE/), U7.6 (E/), U7.7 (VEE), U7.8 (GND), U8.7 (IMODE), U8.9 (PGND), U8.15 (GND), U8.16 (PMODE), U8.17 (PAD), U9.7 (IMODE), U9.9 (PGND), U9.15 (GND), U9.16 (PMODE), U9.17 (PAD), U10.7 (IMODE), U10.9 (PGND), U10.15 (GND), U10.16 (PMODE), U10.17 (PAD), U11.7 (IMODE), U11.9 (PGND), U11.15 (GND), U11.16 (PMODE), U11.17 (PAD), U12.7 (IMODE), U12.9 (PGND), U12.15 (GND), U12.16 (PMODE), U12.17 (PAD), U13.7 (IMODE), U13.9 (PGND), U13.15 (GND), U13.16 (PMODE), U13.17 (PAD), U14.7 (IMODE), U14.9 (PGND), U14.15 (GND), U14.16 (PMODE), U14.17 (PAD)
IPROPI1: R29.2, U8.6 (IPROPI)
IPROPI2: R34.2, U9.6 (IPROPI)
IPROPI3: R39.2, U10.6 (IPROPI)
IPROPI4: R44.2, U11.6 (IPROPI)
IPROPI5: R49.2, U12.6 (IPROPI)
IPROPI6: R91.2, U13.6 (IPROPI)
IPROPI7: R98.2, U14.6 (IPROPI)
ISEN1: C11.2, R21.2, U7.13 (Y0)
ISEN2: C12.2, R22.2, U7.14 (Y1)
ISEN3: C13.2, R23.2, U7.15 (Y2)
ISEN4: C14.2, R24.2, U7.12 (Y3)
ISEN5: C15.2, R25.2, U7.1 (Y4)
ISEN6: C61.2, R95.2, U7.5 (Y5)
ISEN7: C66.2, R102.2, U7.2 (Y6)
LED5_A: D3.2 (A), R4.2
LEDF1_A: D7.2 (A), R31.2
LEDF2_A: D10.2 (A), R36.2
LEDF3_A: D13.2 (A), R41.2
LEDF4_A: D16.2 (A), R46.2
LEDF5_A: D19.2 (A), R51.2
LEDF6_A: D41.2 (A), R93.2
LEDF7_A: D44.2 (A), R100.2
LEDM_A: D2.2 (A), R3.2
M1+: J1.50, R27.1, U8.8 (OUT1)
M1-: J1.17, R28.2, U8.10 (OUT2)
M1LN: D5.1 (K), D6.2 (A), R28.1
M1LP: D5.2 (A), D6.1 (K), R27.2
M2+: J1.49, R32.1, U9.8 (OUT1)
M2-: J1.16, R33.2, U9.10 (OUT2)
M2LN: D8.1 (K), D9.2 (A), R33.1
M2LP: D8.2 (A), D9.1 (K), R32.2
M3+: J1.48, R37.1, U10.8 (OUT1)
M3-: J1.15, R38.2, U10.10 (OUT2)
M3LN: D11.1 (K), D12.2 (A), R38.1
M3LP: D11.2 (A), D12.1 (K), R37.2
M4+: J1.47, R42.1, U11.8 (OUT1)
M4-: J1.14, R43.2, U11.10 (OUT2)
M4LN: D14.1 (K), D15.2 (A), R43.1
M4LP: D14.2 (A), D15.1 (K), R42.2
M5+: J1.46, R47.1, U12.8 (OUT1)
M5-: J1.13, R48.2, U12.10 (OUT2)
M5LN: D17.1 (K), D18.2 (A), R48.1
M5LP: D17.2 (A), D18.1 (K), R47.2
M6+: J1.45, R89.1, U13.8 (OUT1)
M6-: J1.12, R90.2, U13.10 (OUT2)
M6LN: D39.1 (K), D40.2 (A), R90.1
M6LP: D39.2 (A), D40.1 (K), R89.2
M7+: J8.1 (M+), R96.1, U14.8 (OUT1)
M7-: J8.2 (M-), R97.2, U14.10 (OUT2)
M7LN: D42.1 (K), D43.2 (A), R97.1
M7LP: D42.2 (A), D43.1 (K), R96.2
MUX_S0: U6.15 (QA), U7.11 (S0)
MUX_S1: U6.1 (QB), U7.10 (S1)
MUX_S2: U6.2 (QC), U7.9 (S2)
NFLT1: D7.1 (K), R14.2, U3.3 (E), U8.4 (nFAULT)
NFLT2: D10.1 (K), R15.2, U3.4 (F), U9.4 (nFAULT)
NFLT3: D13.1 (K), R16.2, U3.5 (G), U10.4 (nFAULT)
NFLT4: D16.1 (K), R17.2, U3.6 (H), U11.4 (nFAULT)
NFLT5: D19.1 (K), R18.2, U3.11 (A), U12.4 (nFAULT)
NFLT6: D41.1 (K), R94.2, U3.12 (B), U13.4 (nFAULT)
NFLT7: D44.1 (K), R101.2, U3.13 (C), U14.4 (nFAULT)
NSLEEP: Q3.2 (S), R9.1, TP9.1, U8.3 (nSLEEP), U9.3 (nSLEEP), U10.3 (nSLEEP), U11.3 (nSLEEP), U12.3 (nSLEEP), U13.3 (nSLEEP), U14.3 (nSLEEP)
PIX_3V: Q4.2 (S), U1.38 (IO48)
PIX_5V: Q4.3 (D), R52.1, R53.1
PIX_D0: D21.3 (DIN), R52.2
PIX_D1: D21.1 (DOUT), D22.3 (DIN)
PIX_D2: D22.1 (DOUT), D23.3 (DIN)
PIX_D3: D23.1 (DOUT), D24.3 (DIN)
PIX_D4: D24.1 (DOUT), D25.3 (DIN)
PIX_D5: D25.1 (DOUT), D26.3 (DIN)
PIX_D6: D26.1 (DOUT), D27.3 (DIN)
PIX_D7: D27.1 (DOUT), D28.3 (DIN)
PIX_D8: D28.1 (DOUT), D49.3 (DIN)
PIX_D9: D49.1 (DOUT), D50.3 (DIN)
PS_ON: J2.16 (PS_ON), JP1.1
PWM1: U1.8 (IO15), U8.1 (EN/IN1)
PWM2: U1.9 (IO16), U9.1 (EN/IN1)
PWM3: U1.10 (IO17), U10.1 (EN/IN1)
PWM4: U1.11 (IO18), U11.1 (EN/IN1)
PWM5: U1.31 (IO39), U12.1 (EN/IN1)
PWM6: U1.32 (IO38), U13.1 (EN/IN1)
PWM7: U1.15 (IO9), U14.1 (EN/IN1)
SLP: R8.1, U1.28 (IO42)
SLP_D: Q3.3 (D), R8.2
SLP_G: C7.1, Q3.1 (G), R10.1, R11.1
SR_CHAIN: U3.10 (SER), U5.9 (QH)
SR_CHAIN_O: U2.9 (QH'), U6.14 (SER)
SR_LATCH: U1.37 (IO45), U2.12 (RCLK), U3.1 (SH/LD/), U5.1 (SH/LD/), U6.12 (RCLK)
SR_MISO: R12.2, U1.19 (IO13)
SR_MISO_Q: R12.1, U3.9 (QH)
SR_MOSI: U1.14 (IO46), U2.14 (SER)
SR_SCK: R13.2, U1.20 (IO14), U2.11 (SRCLK), U3.2 (CLK), U5.2 (CLK), U6.11 (SRCLK)
SW1: C50.1, R80.2, R81.1, U5.3 (E)
SW1_IN: J1.23, R80.1
SW2: C48.1, R76.2, R77.1, U5.4 (F)
SW2_IN: J1.7, R76.1
SW3: C49.1, R78.2, R79.1, U5.5 (G)
SW3_IN: J1.24, R78.1
SW4: C47.1, R74.2, R75.1, U5.6 (H)
SW4_IN: J1.8, R74.1
SW5: C51.1, R82.2, R83.1, U5.11 (A)
SW5_IN: J1.6, R82.1
SW7: C71.1, R111.2, R112.1, U5.14 (D)
SW7_IN: J8.6 (SW), R111.1
VCP1: C18.1, U8.12 (VCP)
VCP2: C21.1, U9.12 (VCP)
VCP3: C24.1, U10.12 (VCP)
VCP4: C27.1, U11.12 (VCP)
VCP5: C30.1, U12.12 (VCP)
VCP6: C58.1, U13.12 (VCP)
VCP7: C63.1, U14.12 (VCP)
VLED_1: J1.11, R84.2
VLED_2: J1.27, R85.2
VLED_3: J1.10, R86.2
VLED_4: J1.26, R87.2
VLED_5: J1.9, R88.2
VLED_6: J1.25, R113.2
VLED_7: J8.3 (LED), R114.2
VM: C1.1 (+), C2.1 (+), C3.1, C4.1, C18.2, C19.1, C21.2, C22.1, C24.2, C25.1, C27.2, C28.1, C30.2, C31.1, C52.2, C53.2, C54.2, C55.2, C56.2, C58.2, C59.1, C60.2, C63.2, C64.1, C65.2, D1.1 (K), K1.24 (NO2), R1.1, R2.1, R3.1, R5.1, TP5.1, U8.11 (VM), U9.11 (VM), U10.11 (VM), U11.11 (VM), U12.11 (VM), U13.11 (VM), U14.11 (VM)
VSENSE: C5.2, C16.2, R5.2, R26.1, U7.4 (Y7)

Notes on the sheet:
TALOS CONTROLLER, prototype 0.5: seven motor channels (the gripper on the robot connector, the rail on J8), the currents through a multiplexer. See README.md.
Every pin ends in a label with its net name; parts with the same label are connected. Pins with a cross are not connected on purpose.
Channels follow the Eshed controller's axis numbering: 1 base, 2 shoulder, 3 elbow, 4 and 5 the two wrist motors, 6 the gripper (no switch), 7 the rail (on J8). Encoders 1 to 4 on the pulse counters, 5 to 7 counted in software.
POWER ENTRY, FUSES, MOTORS ON RELAY AND E-STOP CHAIN
MICROCONTROLLER: ESP32-S3-DevKitC-1 ON SOCKET STRIPS (this board's own pin assignment, in README.md), ITS 5 V FEED
SHIFT REGISTERS ON THE SPI BUS: U2 direction lines out, U6 (behind U2) the multiplexer's select lines; U3 fault lines in, U5 switches, e-stop and 5 V present in
ANALOG INPUTS: seven motor currents and the motor rail, each filtered, through the multiplexer U7 to the DevKit's ADC1 (IO10)
STATUS PIXELS: ten positions for WS2812C-2020-V6 (not placed by JLCPCB) on 5 V behind a level shifter
MOTOR DRIVERS, channels 1 to 7 (DRV8874 in PH/EN mode), each with its fault lamp and its direction lamp pair
ROBOT CONNECTOR (channels 1 to 6), THE RAIL'S TERMINAL J8 (channel 7), ENCODER AND SWITCH CONDITIONING, ENCODER LED SUPPLY
A ground post (J6) and test pads (TP: bare copper pads, no part). The 10 uF at each driver is in the drivers' band.

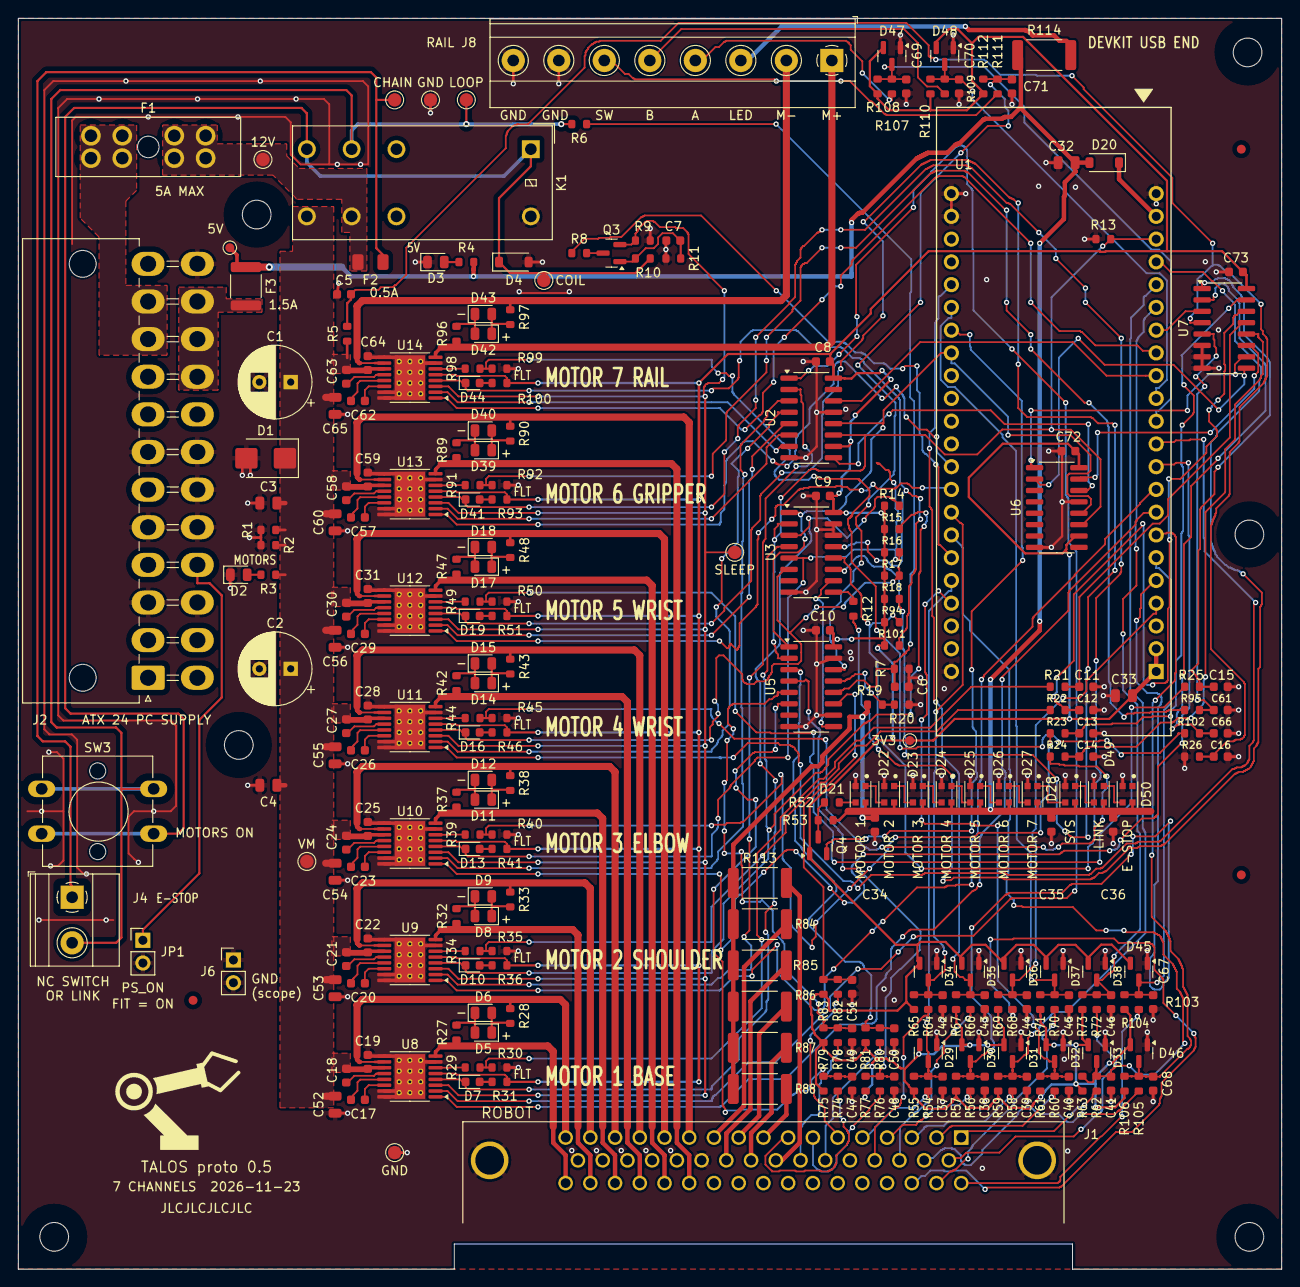
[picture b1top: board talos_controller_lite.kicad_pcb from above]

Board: 2 copper layers, 141.0 x 139.6 mm, 282 parts (0 on the bottom side), 189 nets.

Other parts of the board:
FID1, FID2, FID3: fiducial; Fiducial_1mm_Mask2mm
H1, H2, H3, H4, H5, H6: M3; MountingHole_3.2mm_M3

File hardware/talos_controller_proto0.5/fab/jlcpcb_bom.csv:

Comment,Designator,Footprint,JLCPCB Part #,Manufacturer part (for matching when the number is empty)
10uF 25V,"C3,C4,C32,C33,C52,C53,C54,C55,C56,C60,C65",C_0805_2012Metric,C15850,generic 0805 10uF 25V
100nF,"C5,C6,C8,C9,C10,C11,C12,C13,C14,C15,C16,C18,C19,C21,C22,C24,C25,C27,C28,C30,C31,C34,C35,C36,C47,C48,C49,C50,C51,C58,C59,C61,C63,C64,C66,C71,C72,C73",C_0603_1608Metric,C14663,generic 0603 100nF
10nF,C7,C_0603_1608Metric,C57112,generic 0603 10nF
22nF,"C17,C20,C23,C26,C29,C57,C62",C_0603_1608Metric,C21122,generic 0603 22nF
1nF,"C37,C38,C39,C40,C41,C42,C43,C44,C45,C46,C67,C68,C69,C70",C_0603_1608Metric,C1588,generic 0603 1nF
SMBJ15A,D1,D_SMB,C2760888,SMBJ15A
green,"D2,D3,D5,D6,D8,D9,D11,D12,D14,D15,D17,D18,D39,D40,D42,D43",LED_0805_2012Metric,C2297,Hubei KENTO KT-0805G
1N4148W,D4,D_SOD-123,C81598,1N4148W
red,"D7,D10,D13,D16,D19,D41,D44",LED_0603_1608Metric,C2286,Hubei KENTO KT-0603R
B5819W,D20,D_SOD-123,C8598,B5819W
BAT54S,"D29,D30,D31,D32,D33,D34,D35,D36,D37,D38,D45,D46,D47,D48",SOT-23,C47546,"Nexperia BAT54S,215"
0.5 A fast,F2,Fuse_1206_3216Metric,C151133,Littelfuse 0466.500NRHF
PTC 1.5 A,F3,Fuse_1812_4532Metric,C9308,Littelfuse MINISMDC150F-2
2N7002,"Q3,Q4",SOT-23,C8545,2N7002
3k,"R1,R2,R19",R_0603_1608Metric,C4211,generic 0603 3k
4.7k,"R3,R20,R27,R28,R32,R33,R37,R38,R42,R43,R47,R48,R89,R90,R96,R97",R_0603_1608Metric,C23162,generic 0603 4.7k
2.2k,R4,R_0603_1608Metric,C4190,generic 0603 2.2k
100k,"R5,R11,R13",R_0603_1608Metric,C25803,generic 0603 100k
30k,R6,R_0603_1608Metric,C22984,generic 0603 30k
10k,"R7,R9,R14,R15,R16,R17,R18,R21,R22,R23,R24,R25,R26,R55,R57,R59,R61,R63,R65,R67,R69,R71,R73,R75,R77,R79,R81,R83,R94,R95,R101,R102,R104,R106,R108,R110,R112",R_0603_1608Metric,C25804,generic 0603 10k
1k,"R8,R12,R30,R35,R40,R45,R50,R52,R53,R54,R56,R58,R60,R62,R64,R66,R68,R70,R72,R74,R76,R78,R80,R82,R92,R99,R103,R105,R107,R109,R111",R_0603_1608Metric,C21190,generic 0603 1k
47k,R10,R_0603_1608Metric,C25819,generic 0603 47k
1.5k,"R29,R34,R39,R44,R49,R91,R98",R_0603_1608Metric,C22843,generic 0603 1.5k
470,"R31,R36,R41,R46,R51,R93,R100",R_0603_1608Metric,C23179,generic 0603 470
47 1W,"R84,R85,R86,R87,R88,R113,R114",R_2512_6332Metric,C15261,25121WJ0470T4E
74HC595,"U2,U6",SOIC-16_3.9x9.9mm_P1.27mm,C5947,"Nexperia 74HC595D,118"
74HC165,"U3,U5",SOIC-16_3.9x9.9mm_P1.27mm,C5613,"Nexperia 74HC165D,653 (no substitute)"
74HC4051,U7,SOIC-16_3.9x9.9mm_P1.27mm,C132065,Texas Instruments CD74HC4051M96
DRV8874,"U8,U9,U10,U11,U12,U13,U14",HTSSOP-16-1EP_DRV8874_PWP,C1855818,Texas Instruments DRV8874PWPR
